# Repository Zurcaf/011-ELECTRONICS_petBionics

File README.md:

# PetBionicFirmware

Firmware embarcado do ESP32-C3 para a prótese canina instrumentada **petBionic**:
aquisição de sensores, logging local em cartão SD por sessão e controlo/estado via BLE.

> Este repositório contém **apenas o firmware**. Os restantes componentes do
> projeto vivem em repositórios próprios (app Android, hardware/PCB, análise de
> dados, relatório PIC2).

## Hardware

- Board: **Seeed Studio XIAO ESP32-C3**
- Framework: Arduino (via PlatformIO)
- Sensores: célula de carga **HX711**, IMU **MPU-9250** (+ magnetómetro AK8963)
- Armazenamento: cartão **SD** via SPI

## Estrutura do repositório

```
PetBionicFirmware/
├── platformio.ini          — configuração de build (raiz do projeto PlatformIO)
├── secrets.ini.template    — modelo de credenciais WiFi (copiar para secrets.ini)
├── src/                    — firmware principal
│   ├── core/               — configuração, tipos, pinout, relógio local
│   ├── pipeline/           — pipeline da aplicação (filtros, orientação, eventos)
│   ├── sensors/            — leitura de sensores (RawSensor)
│   ├── storage/            — logging em SD (RawSdLogger)
│   ├── wifi/               — gestão de WiFi
│   ├── web/                — interface web de diagnóstico
│   ├── main.cpp            — entry point do firmware principal
│   └── diagnostic_main.cpp — entry point do firmware de diagnóstico
├── include/                — headers partilhados
├── lib/                    — bibliotecas locais
├── test/                   — testes de bancada e rotinas de calibração
├── experiments/            — sketches Arduino isolados (sensores, BLE, WiFi, SD, deep-sleep)
└── docs/                   — datasheets, diagramas e documentação de referência
```

## Builds

Ambientes definidos em [platformio.ini](platformio.ini):

| Ambiente                    | Descrição                          |
| --------------------------- | ---------------------------------- |
| `seeed_xiao_esp32c3`        | firmware principal                 |
| `seeed_xiao_esp32c3_diag`   | firmware de diagnóstico            |
| `imu_orientation_debug`     | teste de orientação do IMU         |

### Quick start

```bash
pio run -e seeed_xiao_esp32c3
pio run -e seeed_xiao_esp32c3 -t upload
pio device monitor -e seeed_xiao_esp32c3
```

### Credenciais WiFi

`platformio.ini` carrega `secrets.ini` via `extra_configs`. Este ficheiro é
**gitignored** — copia o modelo e preenche os teus valores:

```bash
cp secrets.ini.template secrets.ini
# editar secrets.ini com SSID/PASSWORD reais
```

## Pinout (ESP32-C3 / XIAO)

| Sinal        | Função             | GPIO   | Pino XIAO |
| ------------ | ------------------ | ------ | --------- |
| `kSpiSck`    | SPI SCK            | GPIO21 | D6        |
| `kSpiMiso`   | SPI MISO           | GPIO7  | D5        |
| `kSpiMosi`   | SPI MOSI           | GPIO6  | D4        |
| `kImuCs`     | Chip Select da IMU | GPIO20 | D7        |
| `kSdCs`      | Chip Select do SD  | GPIO11 | D8        |
| `kHx711Dout` | HX711 DOUT         | GPIO10 | D10       |
| `kHx711Sck`  | HX711 SCK          | GPIO9  | D9        |

Definições em [src/core/Pinout.h](src/core/Pinout.h).

## Interface BLE

Serviço GATT custom para comandos e estado:

- Service UUID: `4fafc201-1fb5-459e-8fcc-c5c9c331914b`
- Control UUID: `beb5483e-36e1-4688-b7f5-ea07361b26a8`
- Status UUID:  `beb5483e-36e1-4688-b7f5-ea07361b26a9`

Comandos suportados: `START`, `STOP`, `ALPHA=<0..1>`, `THR=<valor>`,
`PERIOD=<ms>`, `RATE=<hz>`, `TIME=<epoch_s_ou_ms>`, `TIME_SYNC_NOW`.

- `PERIOD=<ms>` atualiza internamente `samplePeriodUs`.
- `RATE=<hz>` converte para período em microssegundos (`1000000/hz`).
- `TIME=` sincroniza o relógio interno usado para timestamps e nomeação de sessão.

## Aquisição e logging

- Amostragem com timeline fixa em microssegundos (default `samplePeriodUs = 12500`, **80 Hz**).
- A sessão SD inicia no `START` e termina no `STOP`.
- Ficheiros CSV por dia/run (ex.: `/20260403/raw_log_20260403_run001_142210_123.csv`).

Header CSV atual:

```csv
t_rel_ms,t_rel_us,time_local,load_cell_raw,load_cell_filt,imu_ax,imu_ay,imu_az,imu_gx,imu_gy,imu_gz,imu_mx,imu_my,imu_mz
```

## Experimentos

Sketches Arduino isolados para testar sensores e conectividade individualmente
estão em [experiments/](experiments/) — ver [experiments/README.md](experiments/README.md).

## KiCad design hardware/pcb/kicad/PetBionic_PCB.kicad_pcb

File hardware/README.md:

# petBionic Hardware

Documentacao de hardware e fabricacao da plataforma petBionic.

## Estrutura

- `hardware/pcb/kicad`
  - Projeto fonte de PCB (KiCad)

- `hardware/pcb/jlcpcb/gerber`
  - Gerbers para fabricacao

- `hardware/pcb/jlcpcb/production_files`
  - Pacote de producao para envio

- `hardware/pcb/production`
  - Artefactos de producao e revisoes

- `hardware/pcb/backups`
  - Backups de trabalho

## Bill of Materials (resumo funcional)

- Seeed Studio XIAO ESP32-C3
- MPU9250 (IMU 9-axis)
- HX711 + celula de carga
- Modulo/cartao SD

## Pinout funcional esperado

- SPI SCK -> D6 (GPIO21)
- SPI MISO -> D5 (GPIO7)
- SPI MOSI -> D4 (GPIO6)
- IMU CS -> D7 (GPIO20)
- SD CS -> D8 (GPIO11)
- HX711 DT -> D10 (GPIO10)
- HX711 CLK -> D9 (GPIO9)

## Fluxo recomendado de revisao

1. Editar no KiCad.
2. Gerar Gerbers e atualizar pasta de producao.
3. Validar pinout contra `firmware/platformio_petBionics/src/core/Pinout.h`.
4. Executar testes de hardware em `firmware/platformio_petBionics/test` apos montagem.

## Integracao com firmware

Qualquer alteracao de pinout no hardware deve ser refletida primeiro em:
- `firmware/platformio_petBionics/src/core/Pinout.h`

Depois disso, validar:
- comunicacao IMU
- escrita no SD
- leitura HX711

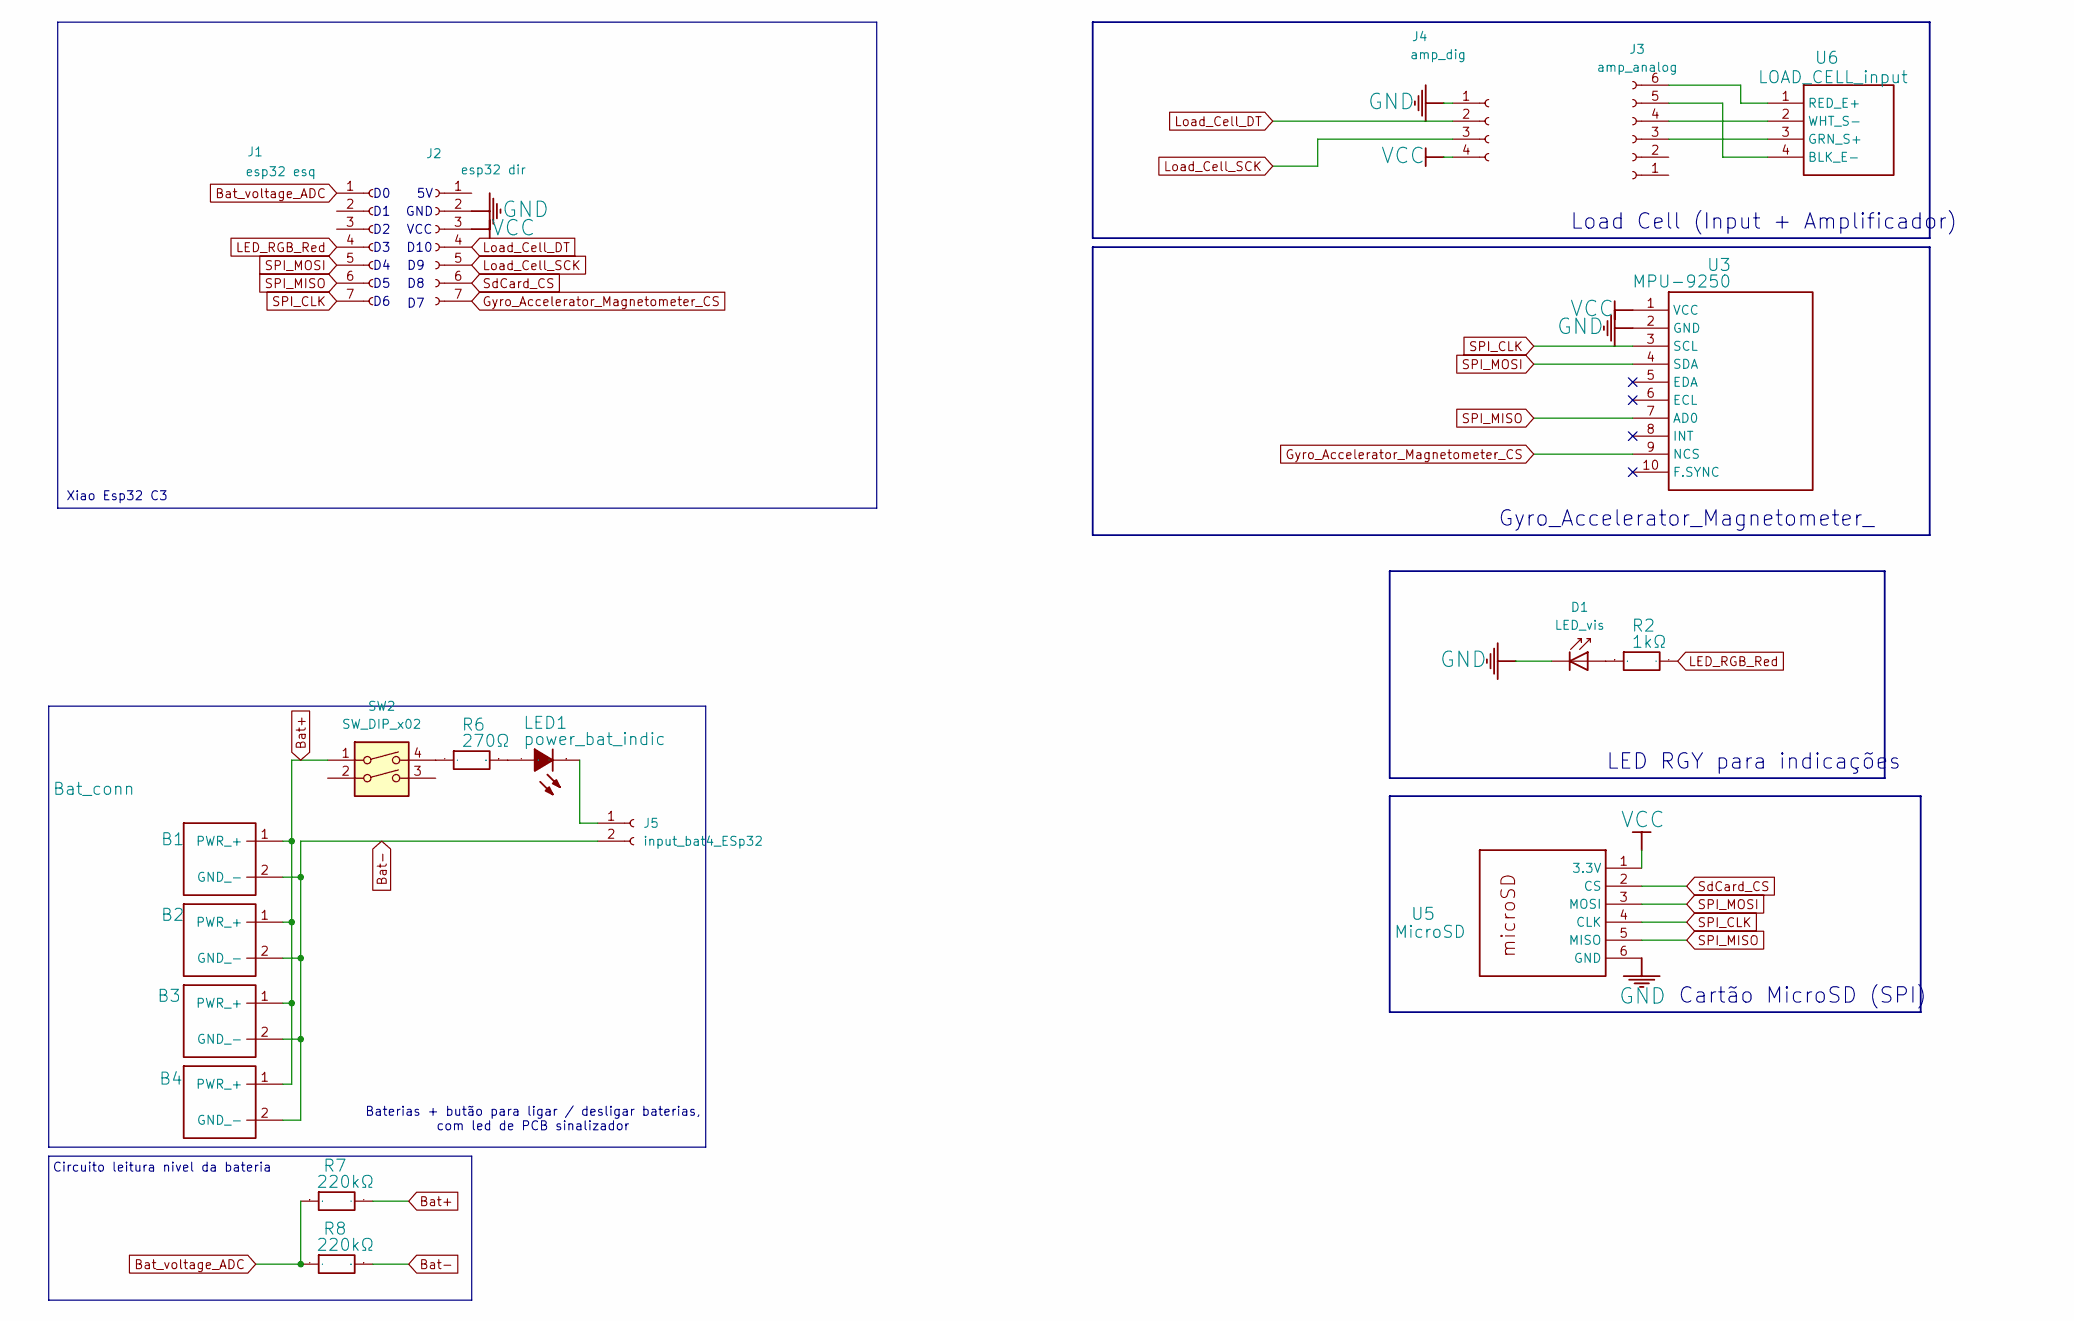
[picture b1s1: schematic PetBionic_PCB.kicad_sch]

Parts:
B1, B2, B3, B4: Bat_conn; PinSocket_1x02_P2.54mm_Vertical
D1: LED_vis; LED_D1.8mm_W3.3mm_H2.4mm
J1: esp32 esq; PinSocket_1x07_P2.54mm_Vertical
J2: esp32 dir; PinSocket_1x07_P2.54mm_Vertical
J3: amp_analog; PinSocket_1x06_P2.54mm_Vertical
J4: amp_dig; PinSocket_1x04_P2.54mm_Vertical
J5: input_bat4_ESp32; PinHeader_1x02_P2.54mm_Vertical
LED1: power_bat_indic; LED_D1.8mm_W3.3mm_H2.4mm; Manufacturer Part LED-0603
R2: 1kΩ; R_Axial_DIN0207_L6.3mm_D2.5mm_P2.54mm_Vertical; Manufacturer Part PTFR0603Q1K00N9
R6: 270Ω; R_Axial_DIN0207_L6.3mm_D2.5mm_P2.54mm_Vertical; Manufacturer Part SCR0603F270R
R7, R8: 220kΩ; R_Axial_DIN0207_L6.3mm_D2.5mm_P2.54mm_Vertical; Manufacturer Part FRR0603F2203TS
SW2: SW_DIP_x02; SW_DIP_SPSTx02_Slide_6.7x6.64mm_W7.62mm_P2.54mm_LowProfile
U3: MPU-9250; PinSocket_1x10_P2.54mm_Vertical
U5: MicroSD; PinSocket_1x06_P2.54mm_Vertical; Manufacturer Part Micro SD TF
U6: LOAD_CELL_input; PinSocket_1x04_P2.54mm_Vertical

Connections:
Bat+: B1.1 (PWR_+), B2.1 (PWR_+), B3.1 (PWR_+), B4.1 (PWR_+), R7.2, SW2.1
Bat-: B1.2 (GND_-), B2.2 (GND_-), B3.2 (GND_-), B4.2 (GND_-), J5.2, R8.1
Bat_voltage_ADC: J1.1, R7.1, R8.2
GND: D1.1 (K), J2.2, J4.1, U3.2 (GND), U5.6 (GND)
Gyro_Accelerator_Magnetometer_CS: J2.7, U3.9 (NCS)
LED_RGB_Red: J1.4, R2.2
Load_Cell_DT: J2.4, J4.2
Load_Cell_SCK: J2.5, J4.3
unnamed: D1.2 (A), R2.1
unnamed: J3.3, U6.3 (GRN_S+)
unnamed: J3.4, U6.2 (WHT_S-)
unnamed: J3.5, U6.4 (BLK_E-)
unnamed: J3.6, U6.1 (RED_E+)
unnamed: J5.1, LED1.1 (-)
unnamed: LED1.2 (+), R6.1
unnamed: R6.2, SW2.4
SPI_CLK: J1.7, U3.3 (SCL), U5.4 (CLK)
SPI_MISO: J1.6, U3.7 (AD0), U5.5 (MISO)
SPI_MOSI: J1.5, U3.4 (SDA), U5.3 (MOSI)
SdCard_CS: J2.6, U5.2 (CS)
VCC: J2.3, J4.4, U3.1 (VCC), U5.1 (3.3V)

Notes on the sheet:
Cartão MicroSD (SPI)
D10
Load Cell (Input + Amplificador)
Gyro_Accelerator_Magnetometer_
Circuito leitura nivel da bateria
VCC
Baterias + butão para ligar / desligar baterias, com led de PCB sinalizador
Xiao Esp32 C3
GND
LED RGY para indicações

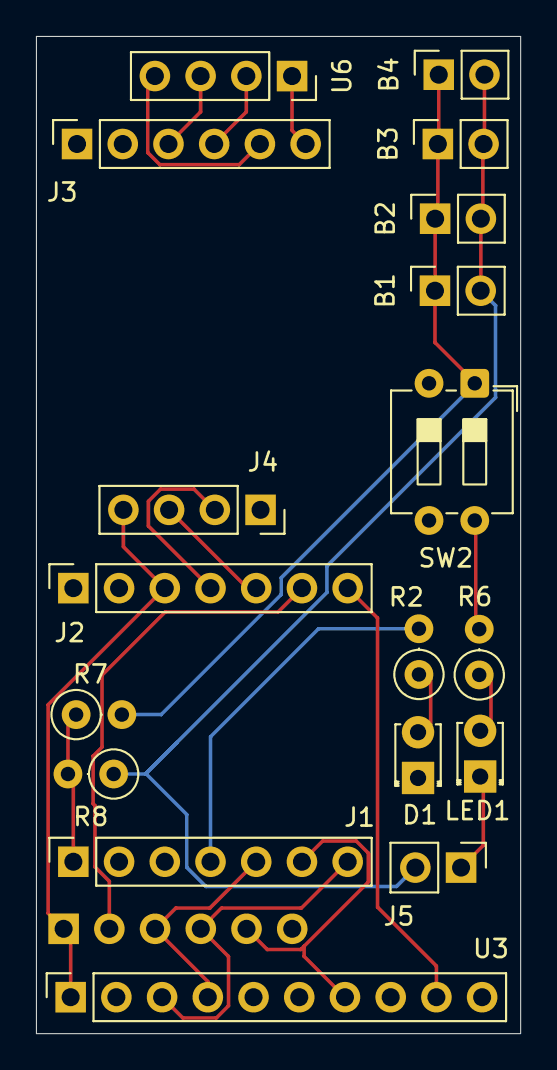
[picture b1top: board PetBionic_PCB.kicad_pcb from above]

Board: 2 copper layers, 26.9 x 55.4 mm, 19 parts (1 on the bottom side), 21 nets.

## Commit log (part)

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2026-02-18 adicionado teste da load_cell e dados estão raw agr
2026-02-20 Add files via upload
    new versions of code
2026-03-02 PCB V1 feita e encomendada
2026-03-04 projectIO criado
2026-03-22 chore: reorganize repo structure and add cross-platform git hygiene
2026-04-02 Readme added
2026-04-03 BLE tranquilo
2026-04-03 BLE connecta e reconneccta tranquilo agr (corrigido esse bug
    state da app estava mal agr está bom e corrigido
2026-04-03 SdCard IMU e HX711 estão com status bom e time sink talvez
2026-04-03 feat: align BLE/app protocol and add session-based IMU logging
    - align Android status UI and automatic time sync retry behavior
    - update BLE commands for PERIOD/RATE and apply system clock sync
    - switch pipeline timing to fixed microsecond schedule (80 Hz default)
    - add magnetometer fields (mx,my,mz) to sensor pipeline and CSV output
    - implement per-session SD logging with day/run file naming
    - add IMU orientation hardware test (roll/pitch/yaw)
2026-04-03 docs: consolidate architecture, app and hardware readmes
    - rewrite root README to reflect current system behavior
    - add central docs hub under docs/README.md
    - add Android app README with structure and BLE contract summary
    - add hardware README with PCB structure, pinout and integration flow
2026-04-03 Improve Android BLE state sync and refresh UI with branded layouts
2026-04-03 Fix BLE status/clock sync and stabilize logging pipeline
2026-04-03 Ignore Android Gradle lock files
2026-04-03 Fix firmware time sync, SD session numbering, and sensor status stability
2026-04-03 Clean tracked local caches and machine-specific artifacts
2026-04-03 Add Wi-Fi and cloud sync flow
2026-04-04 feat: atualizar app e firmware com melhorias de BLE e orientação
2026-04-05 Add WiFi and Firestore sync integration
2026-04-06 Session history working
2026-05-11 Update Android launcher assets and align IMU load test pinout
2026-05-11 Reorganize legacy docs and Arduino IDE archive folders
2026-05-11 Ignore local artifacts and untrack Android Gradle cache
2026-05-18 testes a bateria
2026-05-20 - working local server - start stop and logging hour
2026-05-22 SdCard Local funcional
2026-05-23 Fix SD card file listing and download conflict
    Problem: WebInterface was calling SD.open() directly, conflicting with RawSdLogger's private SPI instance (FSPI), preventing file operations.
    Solution:
    - Added readFileAt() method to RawSdLogger for sequential file reading with offset
    - Added _sdInUse flag to prevent concurrent SD access during active logging
    - Protected listFiles() and getFileSize() to skip when session is active
    - Modified handleDownload() to use RawSdLogger's methods instead of direct SD access
2026-05-23 Fix SD health check blocking access to open session file
    Problem: updateHealth() tried to open the same session file that was already open in _activeFile, causing the health check to fail and mark SD as unavailable.
    Solution: Skip re-opening the session file during health check if a session is already open. Just verify the file handle is valid.
    This fixes the continuous "SD health check failed" messages and allows file listing to work properly.
2026-05-24 Refactor orientation estimation to quaternion-based approach with calibration
    - Implement quaternion-based complementary filter for orientation estimation
    (avoids gimbal lock and handles arbitrary 3D rotations robustly)
    - Add calibrated sensor offsets and biases:
    * Gyroscope bias calibration (°/s)
    * Magnetometer hard-iron and soft-iron corrections
    * Heading offset adjustment
2026-05-24 erros
